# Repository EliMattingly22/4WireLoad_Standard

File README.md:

# 4WireLoad_Standard
A test fixture enabling consistent load measurement facilitating impedance analyzer calibration

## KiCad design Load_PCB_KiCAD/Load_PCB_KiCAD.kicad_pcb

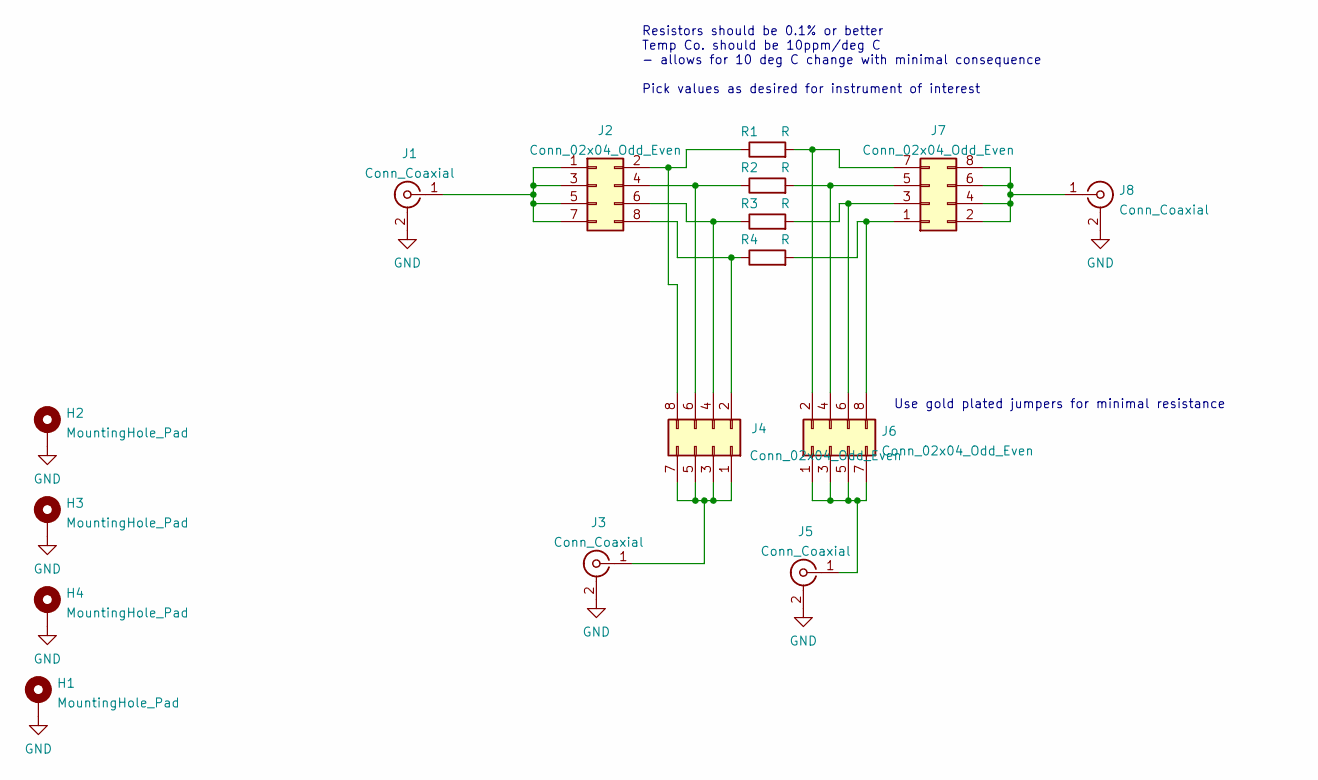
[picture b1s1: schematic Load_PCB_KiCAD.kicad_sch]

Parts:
H1, H2, H3, H4: MountingHole_Pad; MountingHole_3.2mm_M3_Pad
J1, J3, J5, J8: Conn_Coaxial; BNC_Amphenol_B6252HB-NPP3G-50_Horizontal
J2, J4, J6, J7: Conn_02x04_Odd_Even; PinSocket_2x04_P2.54mm_Vertical
R1, R2, R3, R4: R; R_1206_3216Metric_Pad1.30x1.75mm_HandSolder

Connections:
GND: H1.1, H2.1, H3.1, H4.1, J1.2 (Ext), J3.2 (Ext), J5.2 (Ext), J8.2 (Ext)
unnamed: J1.1 (In), J2.1, J2.3, J2.5, J2.7
unnamed: J2.4, J4.6, R2.1
unnamed: J2.6, J4.4, R3.1
unnamed: J3.1 (In), J4.1, J4.3, J4.5, J4.7
unnamed: J2.8, J4.2, R4.1
unnamed: J2.2, J4.8, R1.1
unnamed: J5.1 (In), J6.1, J6.3, J6.5, J6.7
unnamed: J6.2, J7.7, R1.2
unnamed: J6.4, J7.5, R2.2
unnamed: J6.6, J7.3, R3.2
unnamed: J6.8, J7.1, R4.2
unnamed: J7.2, J7.4, J7.6, J7.8, J8.1 (In)

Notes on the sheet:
Use gold plated jumpers for minimal resistance
Resistors should be 0.1% or better Temp Co. should be 10ppm/deg C - allows for 10 deg C change with minimal consequence Pick values as desired for instrument of interest

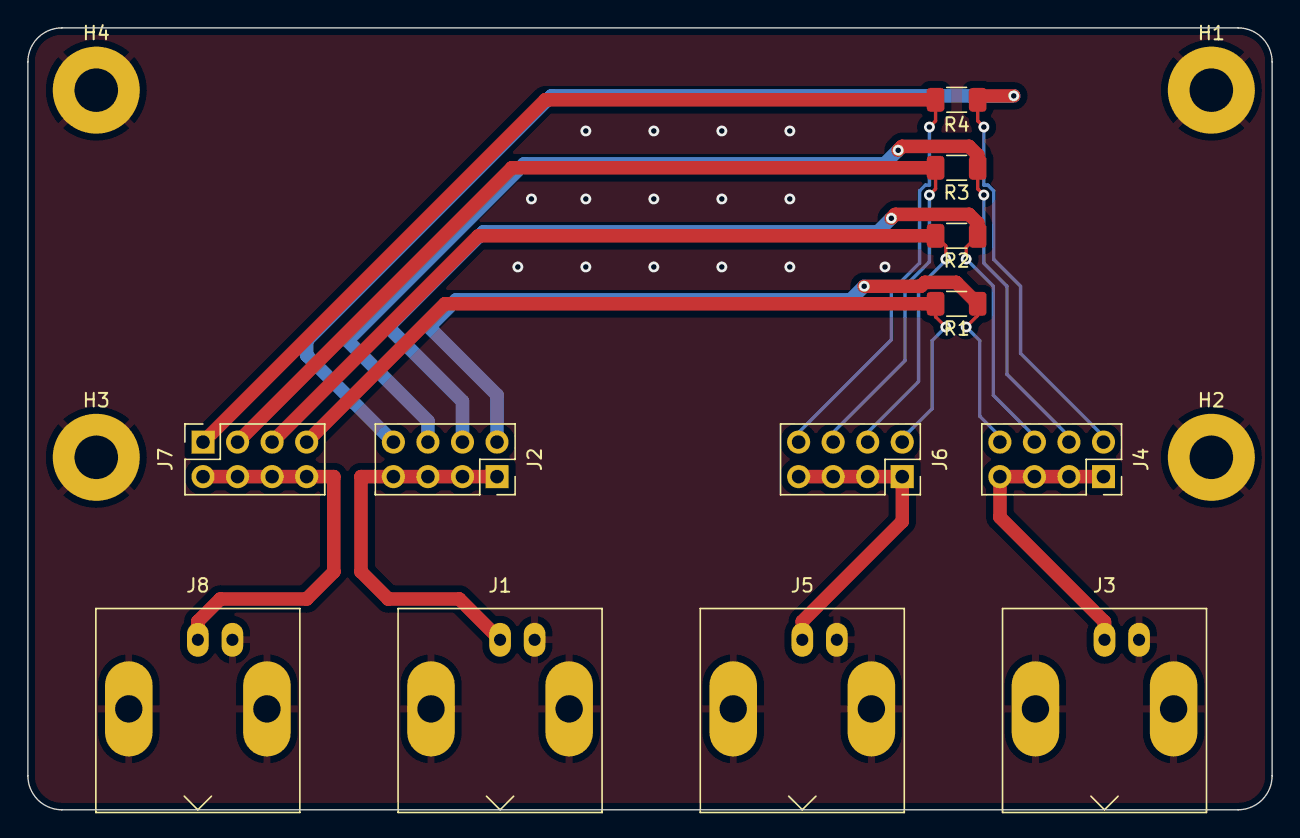
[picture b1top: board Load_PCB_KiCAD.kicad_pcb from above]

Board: 2 copper layers, 91.5 x 57.5 mm, 16 parts (0 on the bottom side), 13 nets.

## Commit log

2022-12-15 Progress update
